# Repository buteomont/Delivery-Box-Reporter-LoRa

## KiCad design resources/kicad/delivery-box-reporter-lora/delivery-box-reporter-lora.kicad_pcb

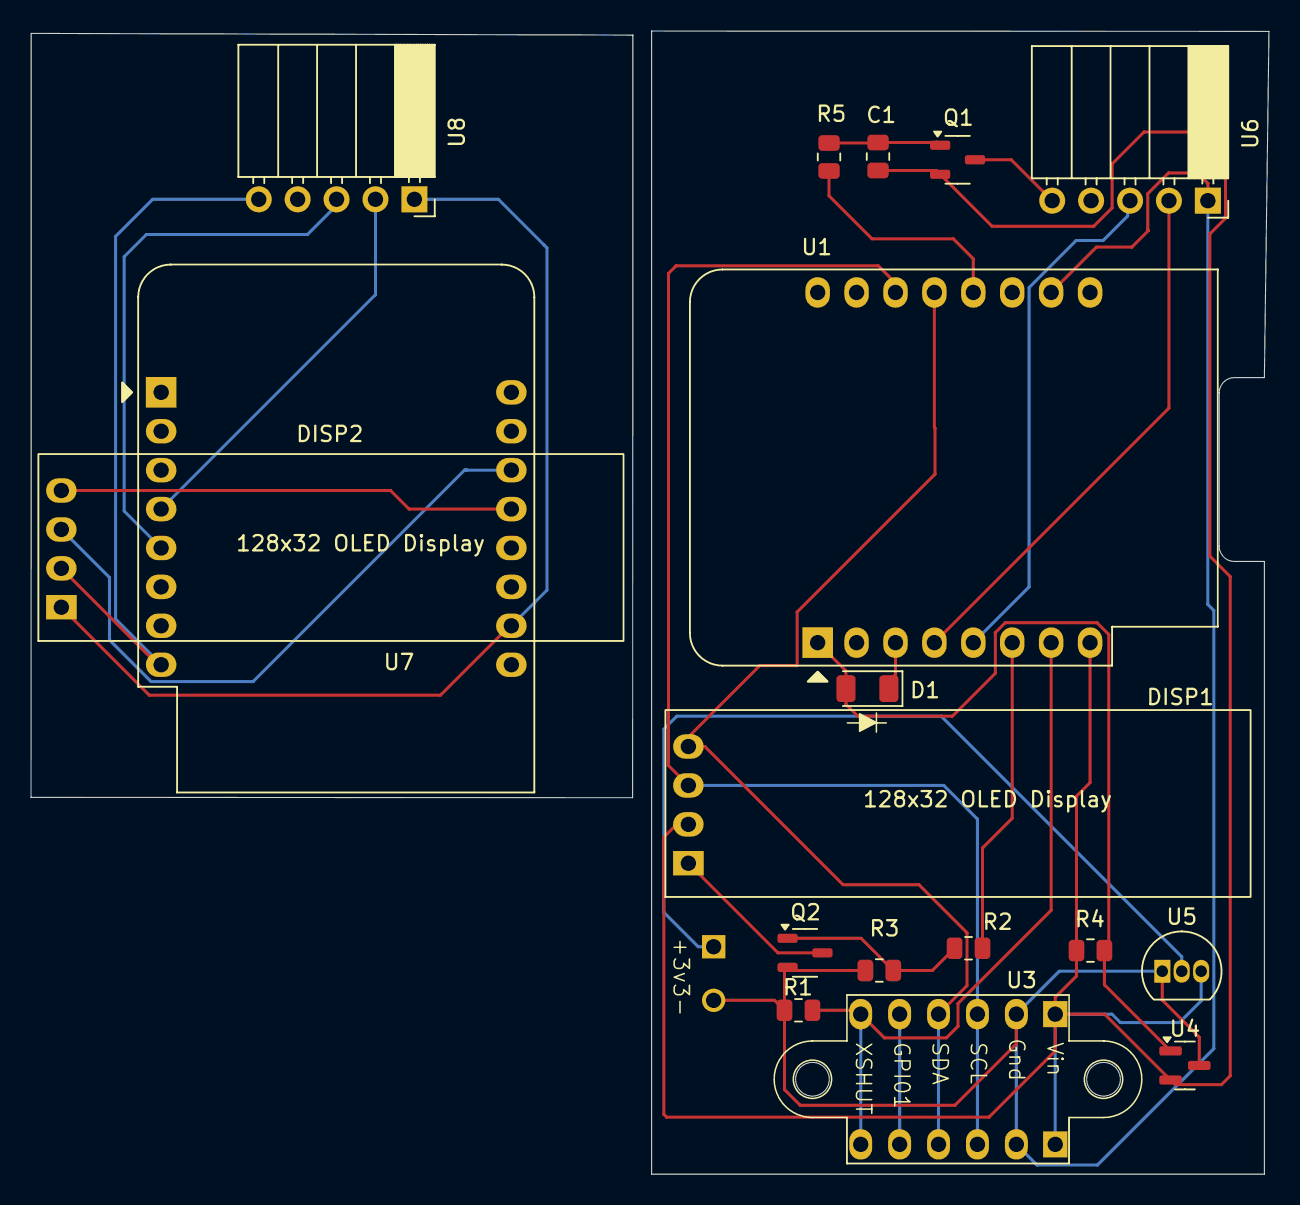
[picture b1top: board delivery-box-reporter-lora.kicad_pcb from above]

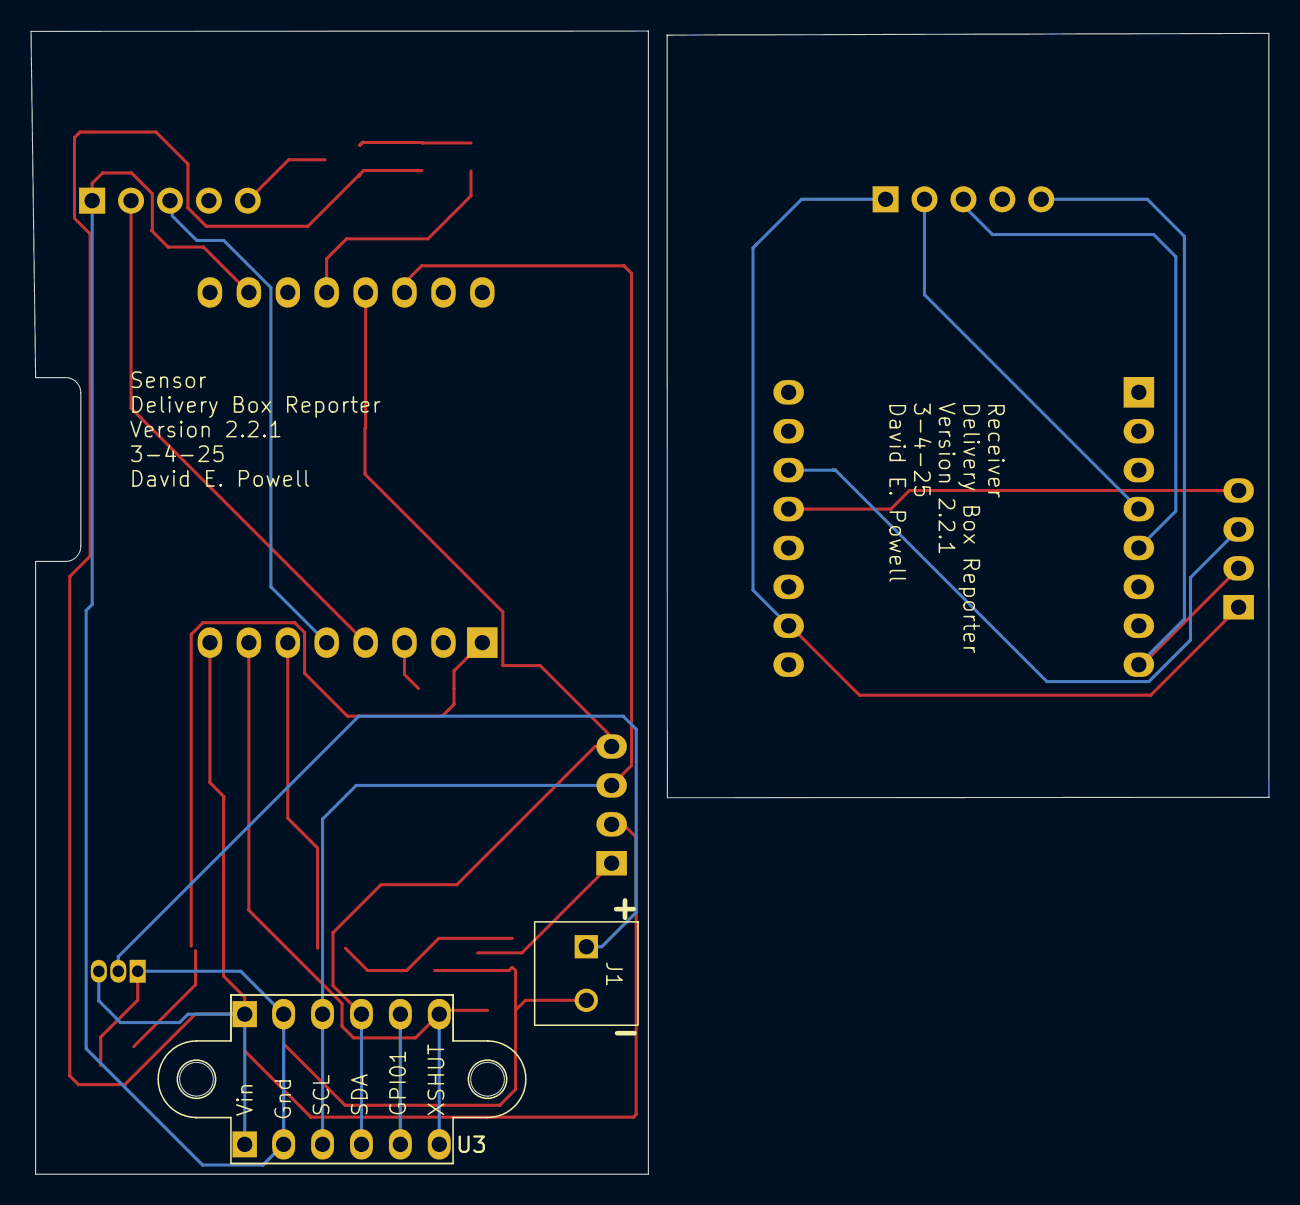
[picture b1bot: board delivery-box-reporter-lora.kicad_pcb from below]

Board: 2 copper layers, 80.8 x 74.6 mm, 20 parts (2 on the bottom side), 22 nets.

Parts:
C1: 22 μF; R_0805_2012Metric
D1: 1N914; D_1206_3216Metric
DISP1, DISP2: 128x32_OLED_Display; OLED_0.91_128x32
J1: Solar Power 4v-6v; KF350 2 Pin Terminal Block
Q1: 2N3906; MMBT3904-7-F_SOT-23-3
Q2: 2N3904; MMBT3904-7-F_SOT-23-3
R1, R2, R3, R4: 10K; R_0805_2012Metric
R5: 1K; R_0805_2012Metric
U1: ESP8266 D1 Mini; WEMOS_D1_mini_light
U3, U3#2: GY-VL53LOX-V2 Distance Sensor
U4: TLV803EA30VDBZR; SOT-23
U5: MCP1702-3302E; TO-92_Inline
U6, U8: PinSocket_1x05_P2.54mm_Horizontal
U7: WeMos_D1_mini; WEMOS_D1_mini_light

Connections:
+3.3V: C1.1, DISP1.2 (Vcc), Q1.2 (E), R4.2, U1.8 (3V3), U3.1 (Vin), U3#2.1 (Vin), U4.2 (V_{DD}), U5.3 (VO)
/LoRa En: R5.1, U1.12 (D3)
/Receiver/3v3B: DISP2.2 (Vcc), U7.8 (3V3), U8.5 (3.3v)
/Receiver/SS RX: U7.4 (SCK/D5), U8.2 (TX)
/Receiver/SS TX: U7.5 (MISO/D6), U8.3 (RX)
/SS RX: U1.4 (SCK/D5), U6.2 (TX)
/SS TX: U1.5 (MISO/D6), U6.3 (RX)
Earth: J1.2, Q2.2 (E), R1.1, R3.1, U1.10 (GND), U3.2 (GND), U3#2.2 (GND), U4.3 (GND), U5.1 (GND), U6.1 (GND)
unnamed: D1.2 (A), R4.1, U1.1 (~RST), U4.1 (RESET)
unnamed: D1.1 (K), U1.3 (D0)
unnamed: DISP1.1 (Gnd), Q2.3 (C)
unnamed: DISP1.3 (SCL), U1.14 (SCL/D1), U3.3 (SCL), U3#2.3 (SCL)
unnamed: DISP1.4 (SDA), U1.13 (SDA/D2), U3.4 (SDA), U3#2.4 (SDA)
unnamed: DISP2.1 (Gnd), U7.10 (GND), U8.1 (GND)
unnamed: DISP2.3 (SCL), U7.14 (SCL/D1)
unnamed: DISP2.4 (SDA), U7.13 (SDA/D2)
unnamed: J1.1, U5.2 (VI)
unnamed: C1.2, Q1.1 (B), R5.2
unnamed: Q1.3 (C), U6.5 (3.3v)
unnamed: Q2.1 (B), R2.1, R3.2
unnamed: R1.2, U1.7 (CS/D8), U3.6 (XSHUT), U3#2.6 (XSHUT)
unnamed: R2.2, U1.6 (MOSI/D7)

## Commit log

2025-01-15 Many updates and fixes
2025-01-15 Finally got the LoRa comm working
2025-01-15 Fixed several bugs in report()
2025-01-15 Added some debug statements
2025-01-15 Unnecessary commit
2025-01-16 updates to presentation
2025-01-18 Found the error that was causing partial messages to be received. SoftwareSerial.begin() needs the isrbuffer 10 times the rcv buffer.
2025-01-18 Recognizes ACK now
2025-01-18 removed some debug prints
2025-01-19 Only change the baud rate after making all other changes!
2025-01-19 Various changes to improve reliablility
2025-01-19 Fixed bogus error due to leftover buffer data
2025-02-05 Mostly changes to the box and board design
2025-02-11 Changes to the enclosures, presentation, and code
2025-02-11 Added check to make sure radio is working during initialization
2025-02-12 Pulled code to enable and disable LORA radio into a separate function
2025-02-14 Updated presentation
2025-02-17 Case and presentation updates
2025-02-21 minor changes
2025-03-05 Small changes to the LoRa power circuit.
